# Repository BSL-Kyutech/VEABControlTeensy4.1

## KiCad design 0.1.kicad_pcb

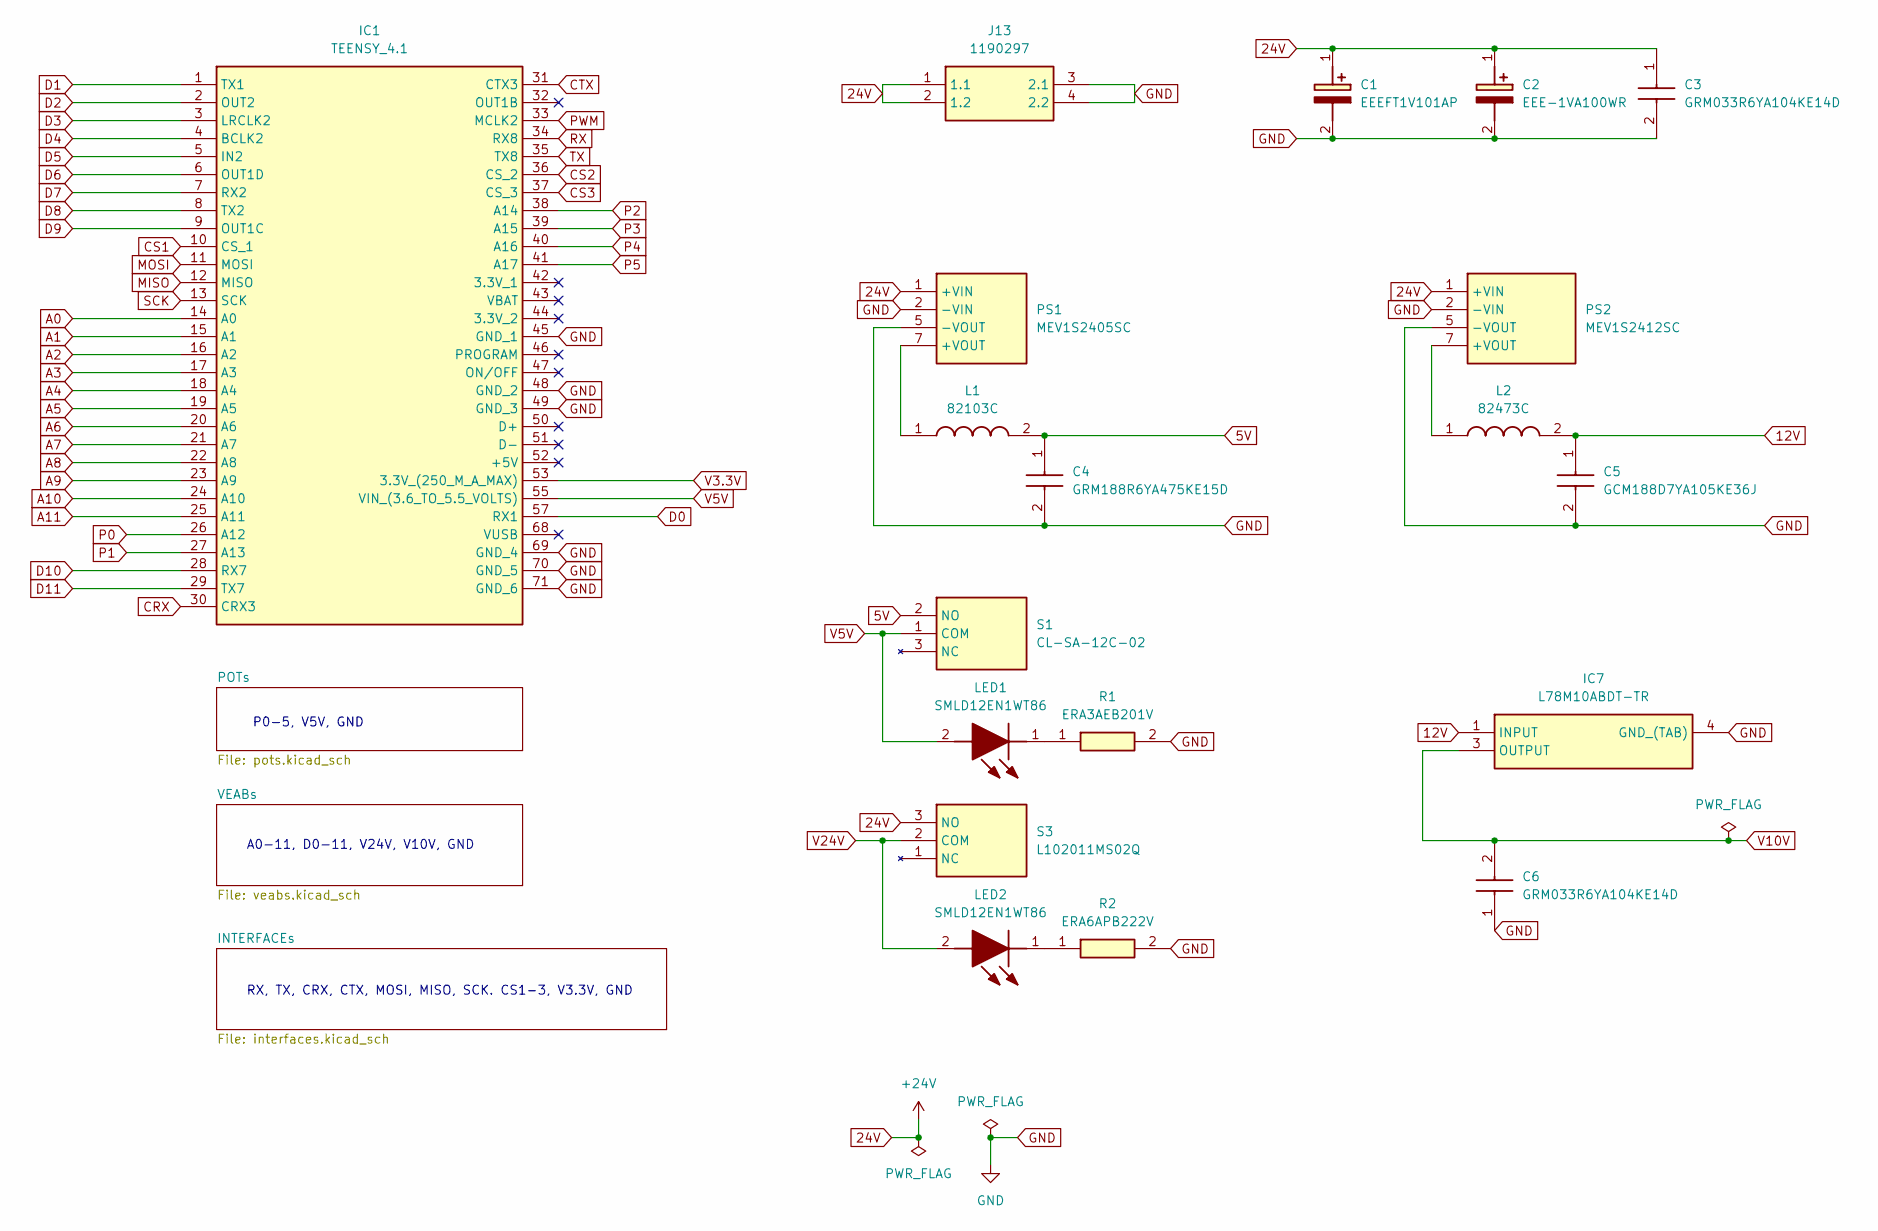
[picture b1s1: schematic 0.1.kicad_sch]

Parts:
C1: EEEFT1V101AP; EEE1AA101SP; Manufacturer_Part_Number EEEFT1V101AP
C2: EEE-1VA100WR; EEE1AA220WR; Manufacturer_Part_Number EEE-1VA100WR; Mouser Part Number 667-EEE-1VA100WR
C3, C6: GRM033R6YA104KE14D; CAPC0603X33N; Manufacturer_Part_Number GRM033R6YA104KE14D; Mouser Part Number 81-GRM33R6YA104KE14D
C4: GRM188R6YA475KE15D; CAPC1608X90N; Manufacturer_Part_Number GRM188R6YA475KE15D; Mouser Part Number 81-GRM188R6YA475KE5D
C5: GCM188D7YA105KE36J; Manufacturer_Part_Number GCM188D7YA105KE36J
IC1: TEENSY_4.1; TEENSY41; Manufacturer_Part_Number TEENSY 4.1
IC7: L78M10ABDT-TR; TO228P972X240-3N; Manufacturer_Part_Number L78M10ABDT-TR; Mouser Part Number 511-L78M10ABDT-TR
J13: 1190297; Manufacturer_Part_Number 1190297; Mouser Part Number 651-1190297
L1: 82103C; 8200; Manufacturer_Part_Number 82103C; Mouser Part Number 580-82103C
L2: 82473C; 8200; Manufacturer_Part_Number 82473C; Mouser Part Number 580-82473C
LED1, LED2: SMLD12EN1WT86; LEDM168X65N; Manufacturer_Part_Number SMLD12EN1WT86; Mouser Part Number 755-SMLD12EN1WT86
PS1: MEV1S2405SC; MEV1_SIP; Manufacturer_Part_Number MEV1S2405SC; Mouser Part Number 580-MEV1S2405SC
PS2: MEV1S2412SC; Manufacturer_Part_Number MEV1S2412SC; Mouser Part Number 580-MEV1S2412SC
R1: ERA3AEB201V; ERA3AEB101V; Manufacturer_Part_Number ERA3AEB201V
R2: ERA6APB222V; ERA6AEB1020V; Manufacturer_Part_Number ERA6APB222V
S1: CL-SA-12C-02; CLSA12C02; Manufacturer_Part_Number CL-SA-12C-02; Mouser Part Number 229-CL-SA-12C-02
S3: L102011MS02Q; Manufacturer_Part_Number L102011MS02Q; Mouser Part Number 611-L102-011

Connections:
5V: C4.1, L1.2, S1.2 (NO); also elsewhere on the board
12V: C5.1, IC7.1 (INPUT), L2.2
24V: C1.1 (+), C2.1 (+), C3.1, J13.1 (1.1), J13.2 (1.2), PS1.1 (+VIN), PS2.1 (+VIN), S3.3 (NO)
A0: IC1.14 (A0); also elsewhere on the board
A1: IC1.15 (A1); also elsewhere on the board
A2: IC1.16 (A2); also elsewhere on the board
A3: IC1.17 (A3); also elsewhere on the board
A4: IC1.18 (A4); also elsewhere on the board
A5: IC1.19 (A5); also elsewhere on the board
A6: IC1.20 (A6); also elsewhere on the board
A7: IC1.21 (A7); also elsewhere on the board
A8: IC1.22 (A8); also elsewhere on the board
A9: IC1.23 (A9); also elsewhere on the board
A10: IC1.24 (A10); also elsewhere on the board
A11: IC1.25 (A11); also elsewhere on the board
CRX: IC1.30 (CRX3); also elsewhere on the board
CS1: IC1.10 (CS_1); also elsewhere on the board
CS2: IC1.36 (CS_2); also elsewhere on the board
CS3: IC1.37 (CS_3); also elsewhere on the board
CTX: IC1.31 (CTX3); also elsewhere on the board
D0: IC1.57 (RX1); also elsewhere on the board
D1: IC1.1 (TX1); also elsewhere on the board
D2: IC1.2 (OUT2); also elsewhere on the board
D3: IC1.3 (LRCLK2); also elsewhere on the board
D4: IC1.4 (BCLK2); also elsewhere on the board
D5: IC1.5 (IN2); also elsewhere on the board
D6: IC1.6 (OUT1D); also elsewhere on the board
D7: IC1.7 (RX2); also elsewhere on the board
D8: IC1.8 (TX2); also elsewhere on the board
D9: IC1.9 (OUT1C); also elsewhere on the board
D10: IC1.28 (RX7); also elsewhere on the board
D11: IC1.29 (TX7); also elsewhere on the board
GND: C1.2 (-), C2.2 (-), C3.2, C4.2, C5.2, C6.1, IC1.45 (GND_1), IC1.48 (GND_2), IC1.49 (GND_3), IC1.69 (GND_4), IC1.70 (GND_5), IC1.71 (GND_6), IC7.4 (GND_(TAB)), J13.3 (2.1), J13.4 (2.2), PS1.2 (-VIN), PS1.5 (-VOUT), PS2.2 (-VIN), PS2.5 (-VOUT), R1.2, R2.2; also elsewhere on the board
MISO: IC1.12 (MISO); also elsewhere on the board
MOSI: IC1.11 (MOSI); also elsewhere on the board
unnamed: LED1.1 (K), R1.1
unnamed: LED2.1 (K), R2.1
unnamed: L1.1, PS1.7 (+VOUT)
unnamed: L2.1, PS2.7 (+VOUT)
P0: IC1.26 (A12); also elsewhere on the board
P1: IC1.27 (A13); also elsewhere on the board
P2: IC1.38 (A14); also elsewhere on the board
P3: IC1.39 (A15); also elsewhere on the board
P4: IC1.40 (A16); also elsewhere on the board
P5: IC1.41 (A17); also elsewhere on the board
PWM: IC1.33 (MCLK2); also elsewhere on the board
RX: IC1.34 (RX8); also elsewhere on the board
SCK: IC1.13 (SCK); also elsewhere on the board
TX: IC1.35 (TX8); also elsewhere on the board
V3.3V: IC1.53 (3.3V_(250_M_A_MAX)); also elsewhere on the board
V5V: IC1.55 (VIN_(3.6_TO_5.5_VOLTS)), LED1.2 (A), S1.1 (COM); also elsewhere on the board
V10V: C6.2, IC7.3 (OUTPUT); also elsewhere on the board
V24V: LED2.2 (A), S3.2 (COM); also elsewhere on the board

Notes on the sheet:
P0-5, V5V, GND
RX, TX, CRX, CTX, MOSI, MISO, SCK. CS1-3, V3.3V, GND
A0-11, D0-11, V24V, V10V, GND

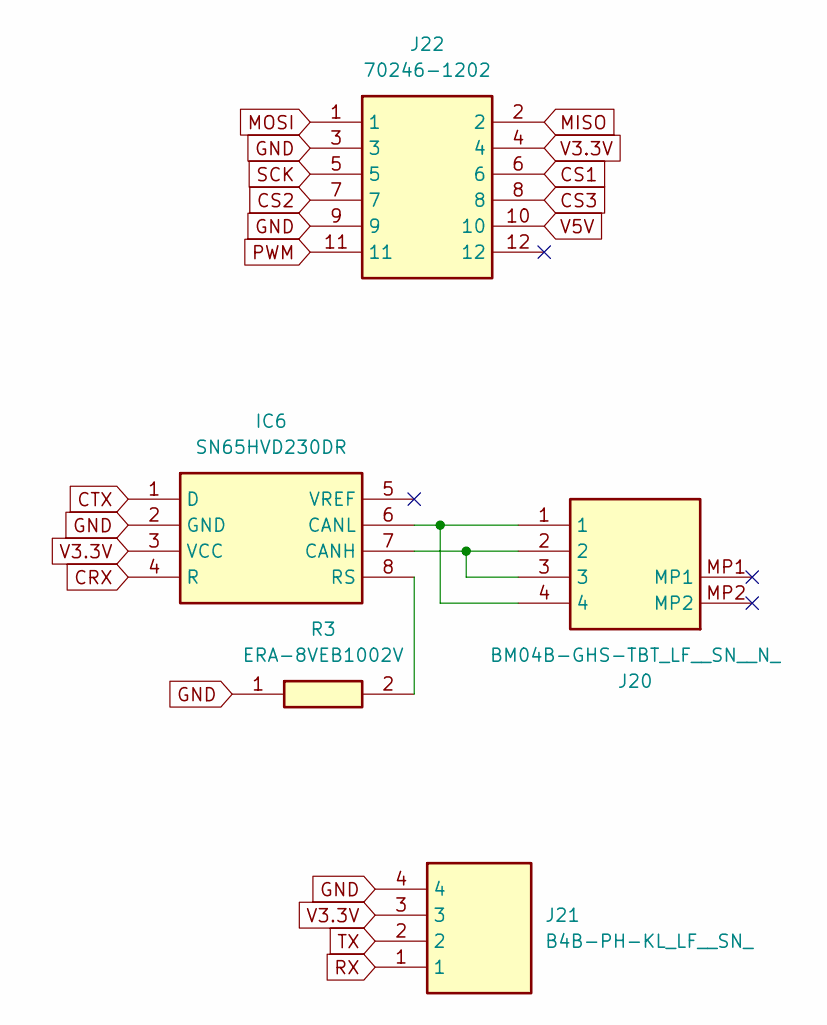
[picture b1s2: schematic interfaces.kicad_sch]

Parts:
IC6: SN65HVD230DR; SOT127P600X175-8N; Manufacturer_Part_Number SN65HVD230DR; Mouser Part Number 595-SN65HVD230DR
J20: BM04B-GHS-TBT_LF__SN__N_; BM04BGHSTBTLFSNN; Manufacturer_Part_Number BM04B-GHS-TBT(LF)(SN)(N)
J21: B4B-PH-KL_LF__SN_; B4BPHKLLFSN; Manufacturer_Part_Number B4B-PH-KL(LF)(SN)
J22: 70246-1202; 702461202; Manufacturer_Part_Number 70246-1202; Mouser Part Number 538-70246-1202
R3: ERA-8VEB1002V; ERA8KEB1004V; Manufacturer_Part_Number ERA-8VEB1002V; Mouser Part Number 667-ERA-8VEB1002V

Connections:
CRX: IC6.4 (R); also elsewhere on the board
CS1: J22.6; also elsewhere on the board
CS2: J22.7; also elsewhere on the board
CS3: J22.8; also elsewhere on the board
CTX: IC6.1 (D); also elsewhere on the board
GND: IC6.2 (GND), J21.4, J22.3, J22.9, R3.1; also elsewhere on the board
MISO: J22.2; also elsewhere on the board
MOSI: J22.1; also elsewhere on the board
unnamed: IC6.7 (CANH), J20.2, J20.3
unnamed: IC6.6 (CANL), J20.1, J20.4
unnamed: IC6.8 (RS), R3.2
PWM: J22.11; also elsewhere on the board
RX: J21.1; also elsewhere on the board
SCK: J22.5; also elsewhere on the board
TX: J21.2; also elsewhere on the board
V3.3V: IC6.3 (VCC), J21.3, J22.4; also elsewhere on the board
V5V: J22.10; also elsewhere on the board

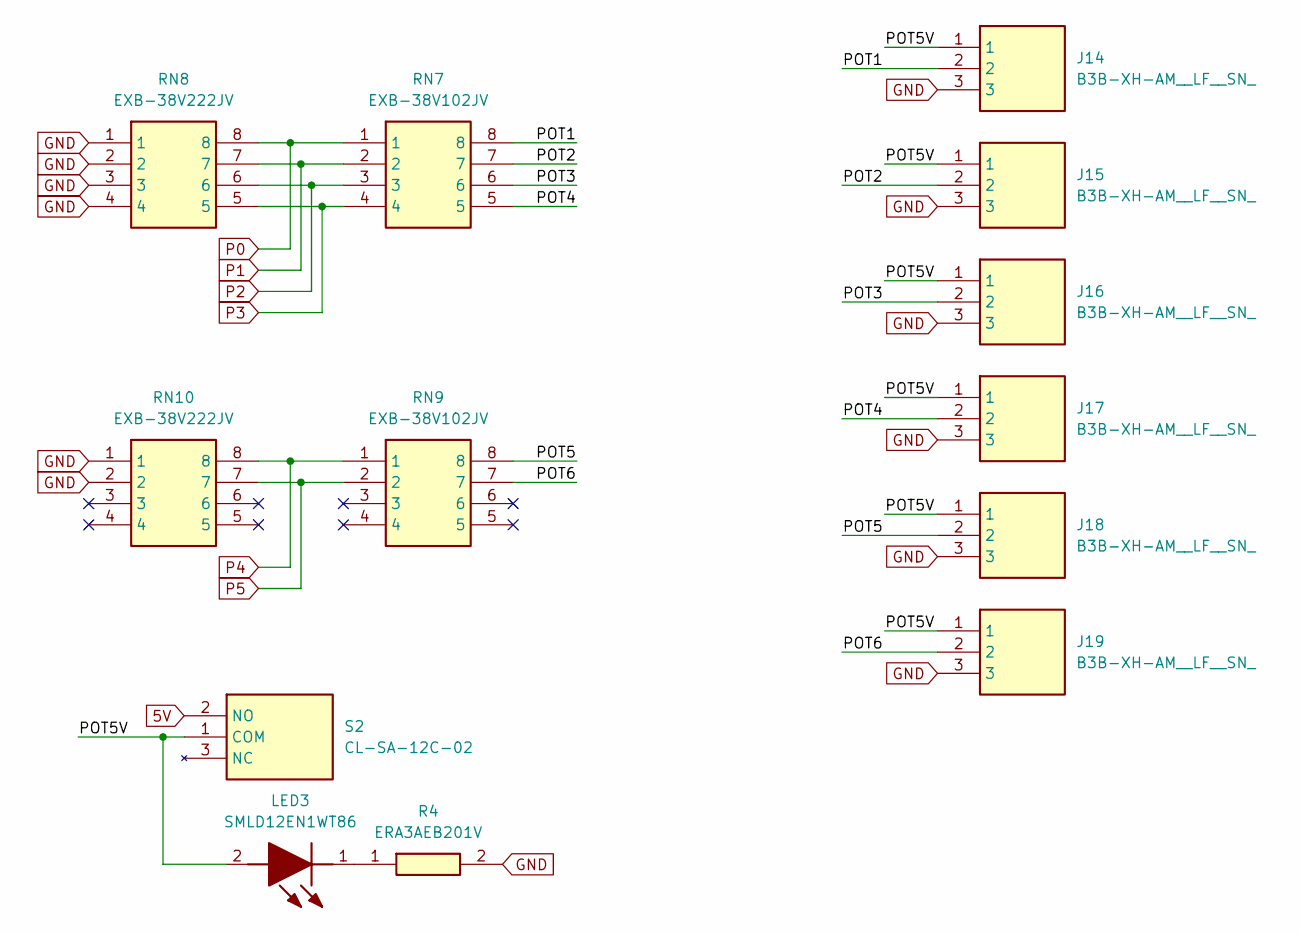
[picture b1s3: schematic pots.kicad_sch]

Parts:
J14, J15, J16, J17, J18, J19: B3B-XH-AM__LF__SN_; B3BXHAMLFSN; Manufacturer_Part_Number B3B-XH-AM (LF)(SN)
LED3: SMLD12EN1WT86; LEDM168X65N; Manufacturer_Part_Number SMLD12EN1WT86; Mouser Part Number 755-SMLD12EN1WT86
R4: ERA3AEB201V; ERA3AEB101V; Manufacturer_Part_Number ERA3AEB201V
RN7, RN9: EXB-38V102JV; EXB38V102JV; Manufacturer_Part_Number EXB-38V102JV; Mouser Part Number 667-EXB-38V102JV
RN8, RN10: EXB-38V222JV; EXB38V472JV; Manufacturer_Part_Number EXB-38V222JV; Mouser Part Number 667-EXB-38V222JV
S2: CL-SA-12C-02; CLSA12C02; Manufacturer_Part_Number CL-SA-12C-02; Mouser Part Number 229-CL-SA-12C-02

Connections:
5V: S2.2 (NO); also elsewhere on the board
/POTs/POT1: J14.2, RN7.8
/POTs/POT2: J15.2, RN7.7
/POTs/POT3: J16.2, RN7.6
/POTs/POT4: J17.2, RN7.5
/POTs/POT5: J18.2, RN9.8
/POTs/POT5V: J14.1, J15.1, J16.1, J17.1, J18.1, J19.1, LED3.2 (A), S2.1 (COM)
/POTs/POT6: J19.2, RN9.7
GND: J14.3, J15.3, J16.3, J17.3, J18.3, J19.3, R4.2, RN8.1, RN8.2, RN8.3, RN8.4, RN10.1, RN10.2; also elsewhere on the board
unnamed: LED3.1 (K), R4.1
P0: RN7.1, RN8.8; also elsewhere on the board
P1: RN7.2, RN8.7; also elsewhere on the board
P2: RN7.3, RN8.6; also elsewhere on the board
P3: RN7.4, RN8.5; also elsewhere on the board
P4: RN9.1, RN10.8; also elsewhere on the board
P5: RN9.2, RN10.7; also elsewhere on the board

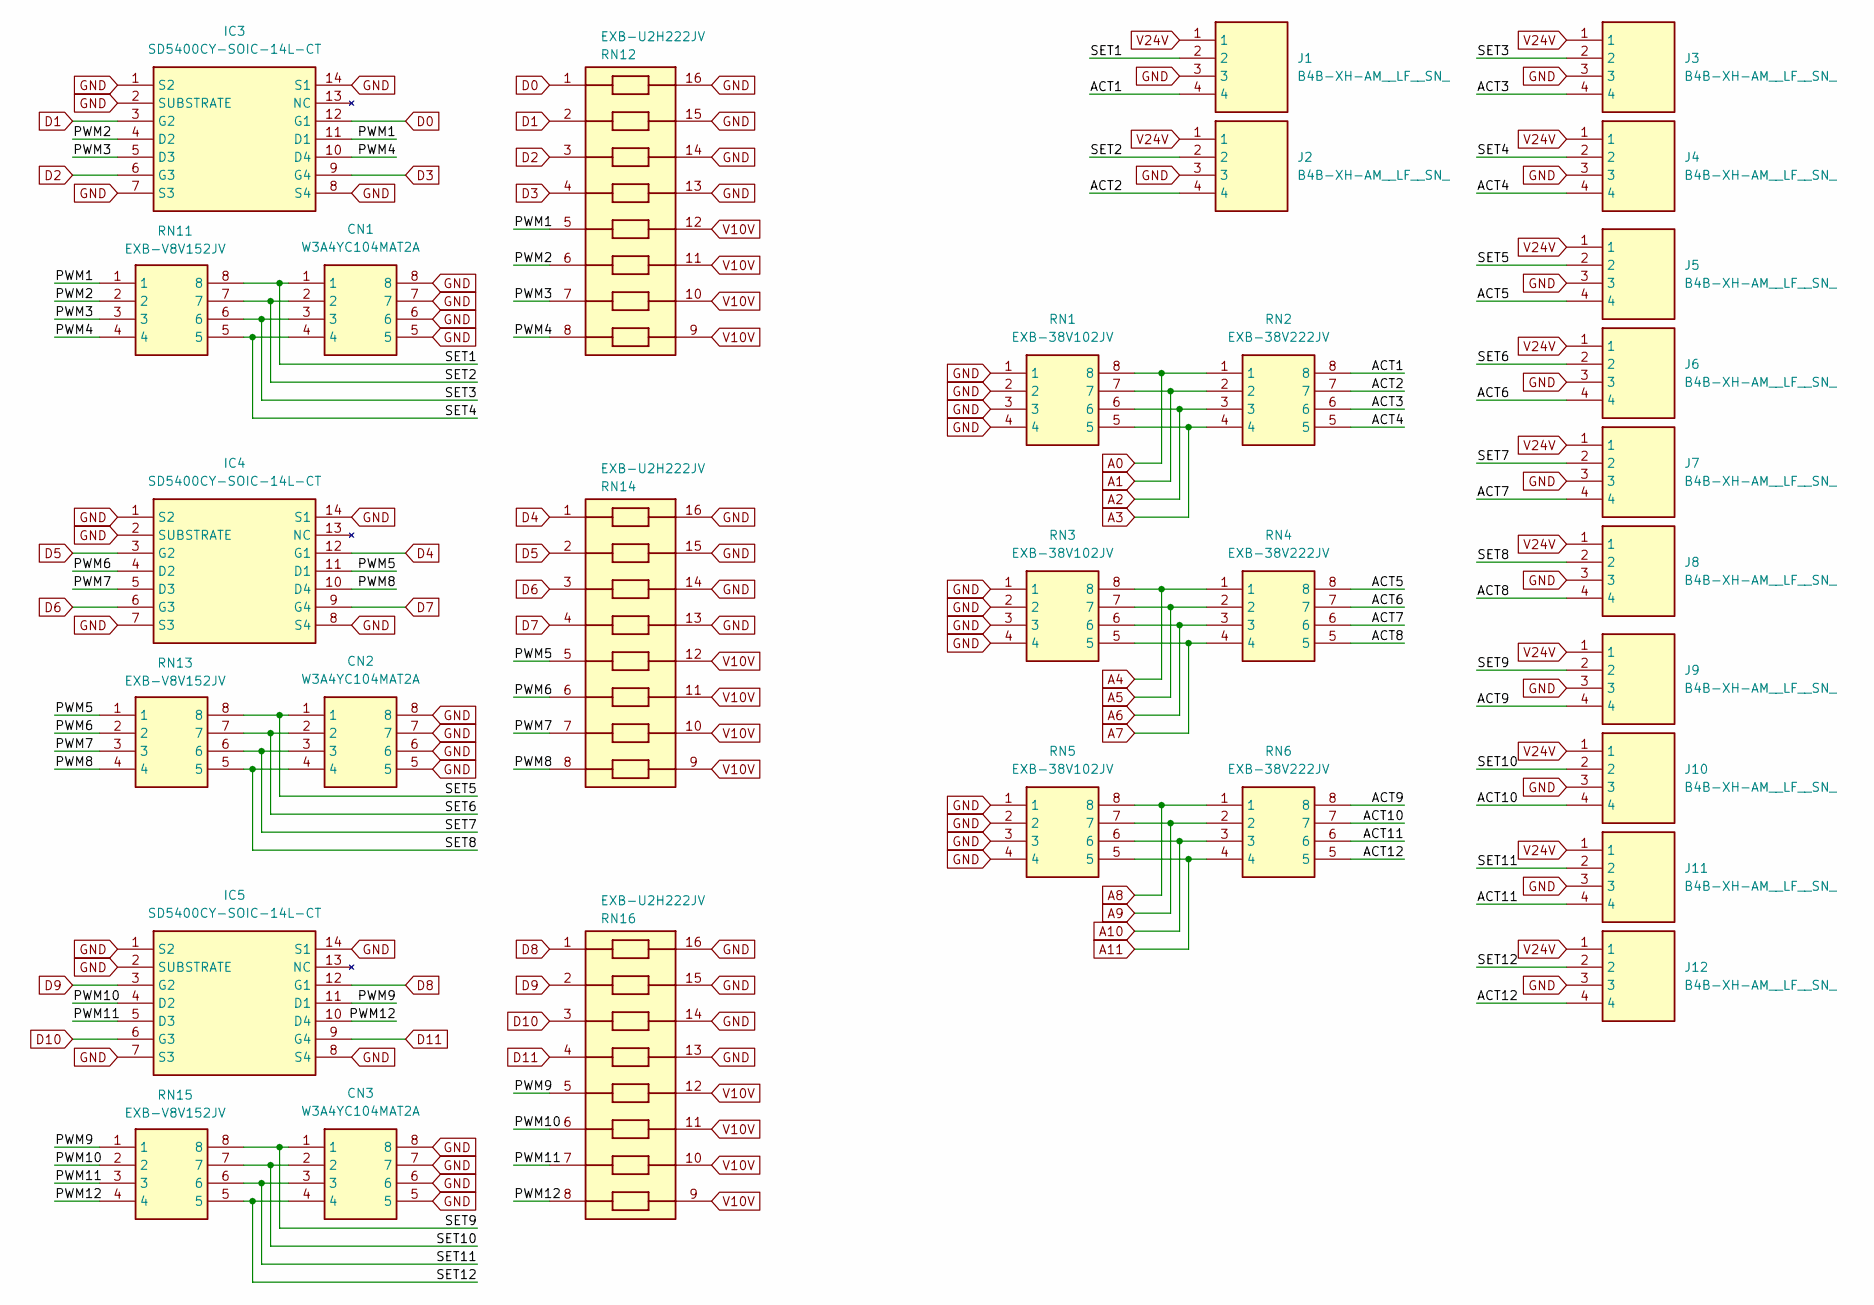
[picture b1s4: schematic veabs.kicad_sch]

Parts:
CN1, CN2, CN3: W3A4YC104MAT2A; Manufacturer_Part_Number W3A4YC104MAT2A; Mouser Part Number 581-W3A4YC104MAT2A
IC3, IC4, IC5: SD5400CY-SOIC-14L-CT; SOIC127P600X175-14N; Manufacturer_Part_Number SD5400CY-SOIC-14L-CT; Mouser Part Number 722-D5400CYSOIC14LCT
J1, J2, J3, J4, J5, J6, J7, J8, J9, J10, J11, J12: B4B-XH-AM__LF__SN_; B4BXHAMLFSN; Manufacturer_Part_Number B4B-XH-AM (LF)(SN)
RN1, RN3, RN5: EXB-38V102JV; EXB38V102JV; Manufacturer_Part_Number EXB-38V102JV; Mouser Part Number 667-EXB-38V102JV
RN2, RN4, RN6: EXB-38V222JV; EXB38V472JV; Manufacturer_Part_Number EXB-38V222JV; Mouser Part Number 667-EXB-38V222JV
RN11, RN13, RN15: EXB-V8V152JV; EXB38V472JV; Manufacturer_Part_Number EXB-V8V152JV; Mouser Part Number 667-EXB-V8V152JV
RN12, RN14, RN16: EXB-U2H222JV; EXBU2H; Manufacturer_Part_Number EXB-U2H222JV; Mouser Part Number 667-EXB-U2H222JV

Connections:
/VEABs/ACT1: J1.4, RN2.8
/VEABs/ACT2: J2.4, RN2.7
/VEABs/ACT3: J3.4, RN2.6
/VEABs/ACT4: J4.4, RN2.5
/VEABs/ACT5: J5.4, RN4.8
/VEABs/ACT6: J6.4, RN4.7
/VEABs/ACT7: J7.4, RN4.6
/VEABs/ACT8: J8.4, RN4.5
/VEABs/ACT9: J9.4, RN6.8
/VEABs/ACT10: J10.4, RN6.7
/VEABs/ACT11: J11.4, RN6.6
/VEABs/ACT12: J12.4, RN6.5
/VEABs/PWM1: IC3.11 (D1), RN11.1, RN12.5
/VEABs/PWM2: IC3.4 (D2), RN11.2, RN12.6
/VEABs/PWM3: IC3.5 (D3), RN11.3, RN12.7
/VEABs/PWM4: IC3.10 (D4), RN11.4, RN12.8
/VEABs/PWM5: IC4.11 (D1), RN13.1, RN14.5
/VEABs/PWM6: IC4.4 (D2), RN13.2, RN14.6
/VEABs/PWM7: IC4.5 (D3), RN13.3, RN14.7
/VEABs/PWM8: IC4.10 (D4), RN13.4, RN14.8
/VEABs/PWM9: IC5.11 (D1), RN15.1, RN16.5
/VEABs/PWM10: IC5.4 (D2), RN15.2, RN16.6
/VEABs/PWM11: IC5.5 (D3), RN15.3, RN16.7
/VEABs/PWM12: IC5.10 (D4), RN15.4, RN16.8
/VEABs/SET1: CN1.1, J1.2, RN11.8
/VEABs/SET2: CN1.2, J2.2, RN11.7
/VEABs/SET3: CN1.3, J3.2, RN11.6
/VEABs/SET4: CN1.4, J4.2, RN11.5
/VEABs/SET5: CN2.1, J5.2, RN13.8
/VEABs/SET6: CN2.2, J6.2, RN13.7
/VEABs/SET7: CN2.3, J7.2, RN13.6
/VEABs/SET8: CN2.4, J8.2, RN13.5
/VEABs/SET9: CN3.1, J9.2, RN15.8
/VEABs/SET10: CN3.2, J10.2, RN15.7
/VEABs/SET11: CN3.3, J11.2, RN15.6
/VEABs/SET12: CN3.4, J12.2, RN15.5
A0: RN1.8, RN2.1; also elsewhere on the board
A1: RN1.7, RN2.2; also elsewhere on the board
A2: RN1.6, RN2.3; also elsewhere on the board
A3: RN1.5, RN2.4; also elsewhere on the board
A4: RN3.8, RN4.1; also elsewhere on the board
A5: RN3.7, RN4.2; also elsewhere on the board
A6: RN3.6, RN4.3; also elsewhere on the board
A7: RN3.5, RN4.4; also elsewhere on the board
A8: RN5.8, RN6.1; also elsewhere on the board
A9: RN5.7, RN6.2; also elsewhere on the board
A10: RN5.6, RN6.3; also elsewhere on the board
A11: RN5.5, RN6.4; also elsewhere on the board
D0: IC3.12 (G1), RN12.1; also elsewhere on the board
D1: IC3.3 (G2), RN12.2; also elsewhere on the board
D2: IC3.6 (G3), RN12.3; also elsewhere on the board
D3: IC3.9 (G4), RN12.4; also elsewhere on the board
D4: IC4.12 (G1), RN14.1; also elsewhere on the board
D5: IC4.3 (G2), RN14.2; also elsewhere on the board
D6: IC4.6 (G3), RN14.3; also elsewhere on the board
D7: IC4.9 (G4), RN14.4; also elsewhere on the board
D8: IC5.12 (G1), RN16.1; also elsewhere on the board
D9: IC5.3 (G2), RN16.2; also elsewhere on the board
D10: IC5.6 (G3), RN16.3; also elsewhere on the board
D11: IC5.9 (G4), RN16.4; also elsewhere on the board
GND: CN1.5, CN1.6, CN1.7, CN1.8, CN2.5, CN2.6, CN2.7, CN2.8, CN3.5, CN3.6, CN3.7, CN3.8, IC3.1 (S2), IC3.2 (SUBSTRATE), IC3.7 (S3), IC3.8 (S4), IC3.14 (S1), IC4.1 (S2), IC4.2 (SUBSTRATE), IC4.7 (S3), IC4.8 (S4), IC4.14 (S1), IC5.1 (S2), IC5.2 (SUBSTRATE), IC5.7 (S3), IC5.8 (S4), IC5.14 (S1), J1.3, J2.3, J3.3, J4.3, J5.3, J6.3, J7.3, J8.3, J9.3, J10.3, J11.3, J12.3, RN1.1, RN1.2, RN1.3, RN1.4, RN3.1, RN3.2, RN3.3, RN3.4, RN5.1, RN5.2, RN5.3, RN5.4, RN12.13, RN12.14, RN12.15, RN12.16, RN14.13, RN14.14, RN14.15, RN14.16, RN16.13, RN16.14, RN16.15, RN16.16; also elsewhere on the board
V10V: RN12.9, RN12.10, RN12.11, RN12.12, RN14.9, RN14.10, RN14.11, RN14.12, RN16.9, RN16.10, RN16.11, RN16.12; also elsewhere on the board
V24V: J1.1, J2.1, J3.1, J4.1, J5.1, J6.1, J7.1, J8.1, J9.1, J10.1, J11.1, J12.1; also elsewhere on the board

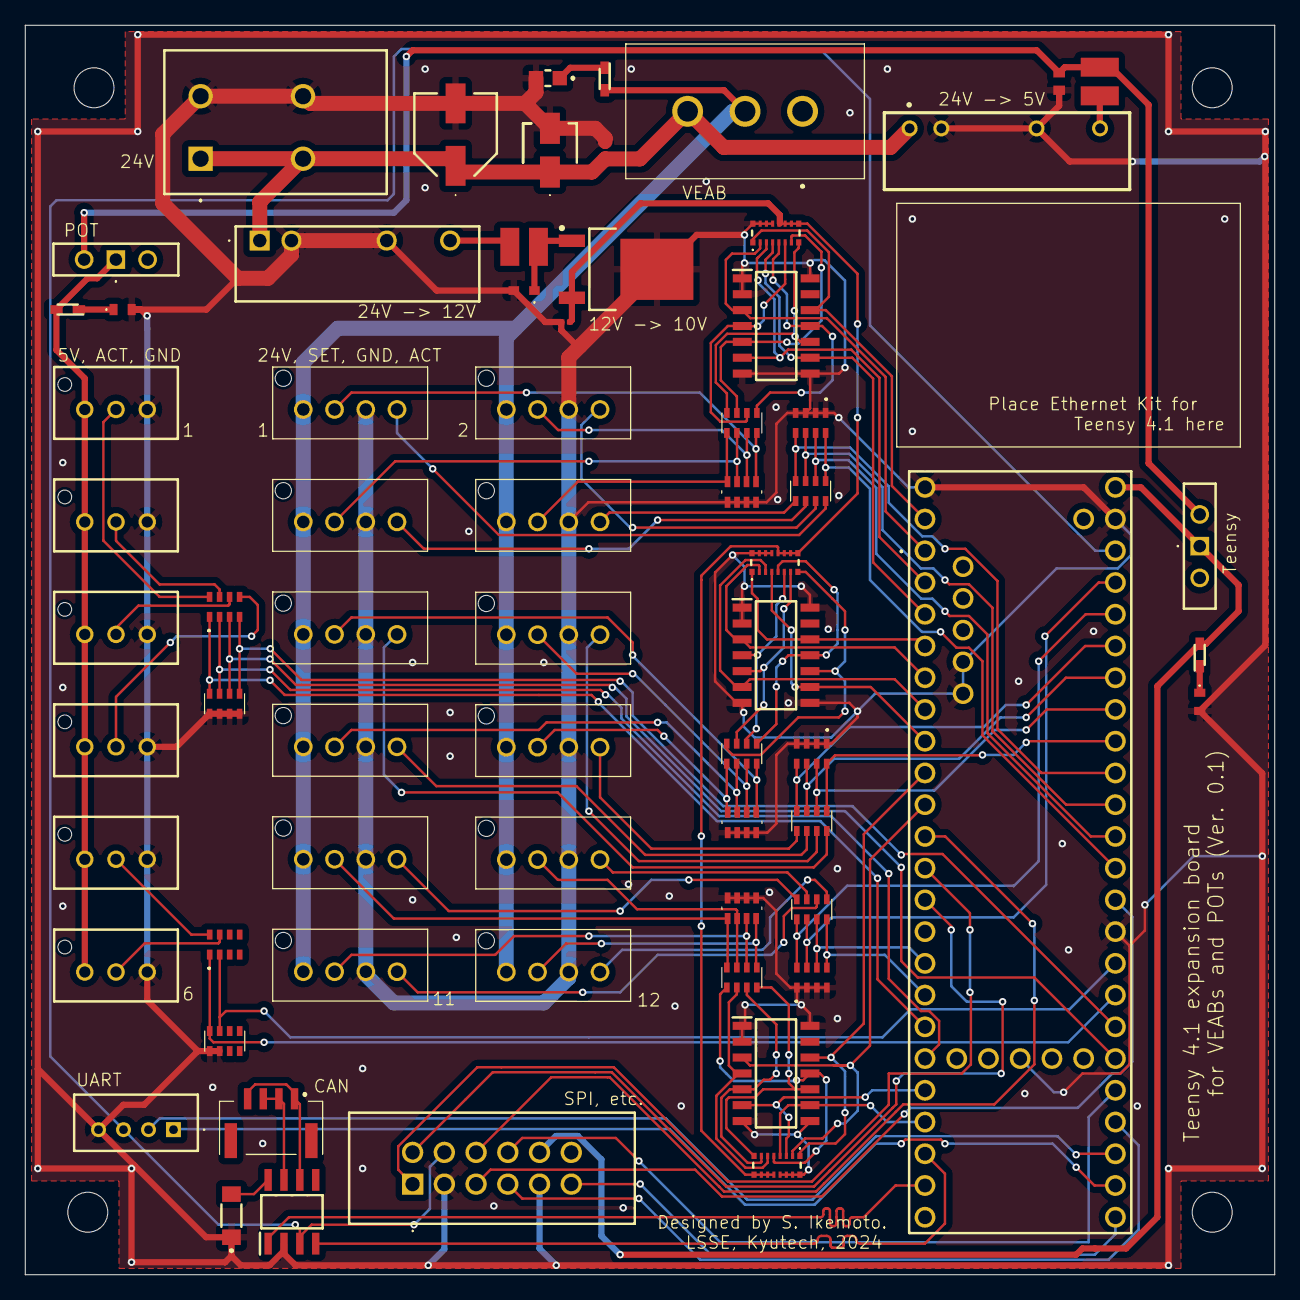
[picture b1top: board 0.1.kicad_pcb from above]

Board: 2 copper layers, 100.0 x 100.0 mm, 67 parts (0 on the bottom side), 100 nets.
